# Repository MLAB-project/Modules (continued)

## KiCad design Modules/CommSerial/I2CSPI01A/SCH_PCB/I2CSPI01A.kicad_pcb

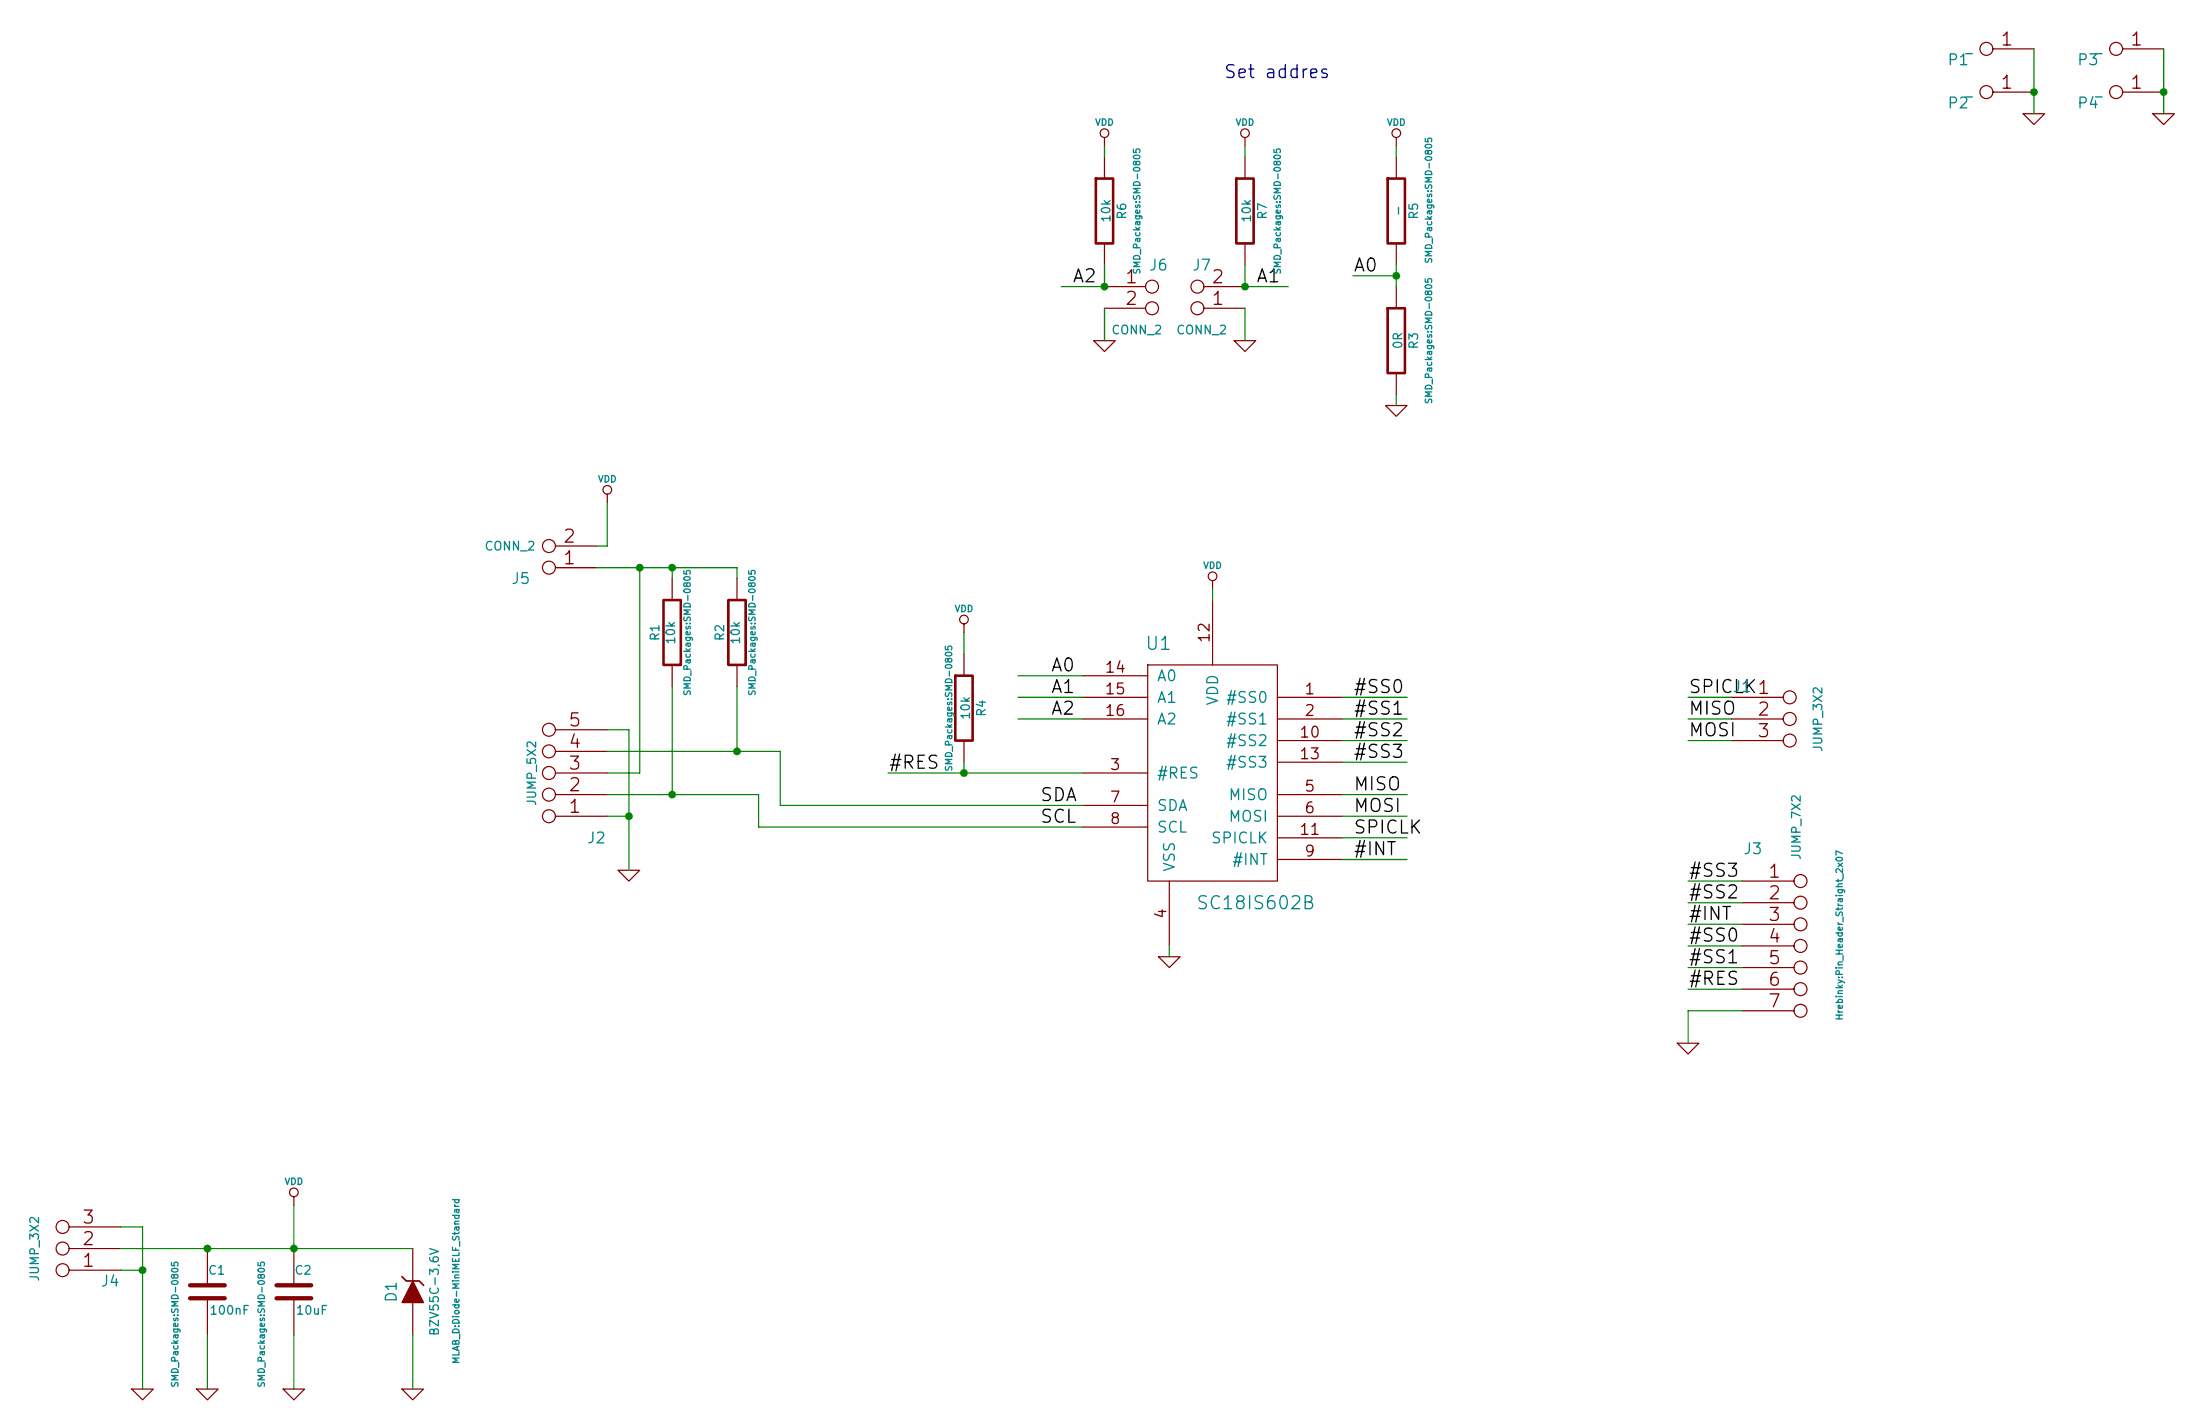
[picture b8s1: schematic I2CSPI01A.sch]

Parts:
C1: 100nF; SMD-0805
C2: 10uF; SMD-0805
D1: BZV55C-3,6V; Diode-MiniMELF_Standard
J1, J4: JUMP_3X2; Pin_Header_Straight_2x03
J2: JUMP_5X2; Pin_Header_Straight_2x05
J3: JUMP_7X2; Pin_Header_Straight_2x07
J5, J6, J7: CONN_2; Pin_Header_Straight_1x02
P1, P2, P3, P4: _; MountingHole_3mm
R1, R2, R4, R6, R7: 10k; SMD-0805
R3: 0R; SMD-0805
R5: -; SMD-0805
U1: SC18IS602B; TSSOP-16

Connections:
/#INT: J3.3, J3.12, U1.9 (#INT)
/#RES: J3.6, J3.9, R4.2, U1.3 (#RES)
/#SS0: J3.4, J3.11, U1.1 (#SS0)
/#SS1: J3.5, J3.10, U1.2 (#SS1)
/#SS2: J3.2, J3.13, U1.10 (#SS2)
/#SS3: J3.1, J3.14, U1.13 (#SS3)
/A0: R3.1, R5.2, U1.14 (A0)
/A1: J7.2 (PM), R7.2, U1.15 (A1)
/A2: J6.1, R6.2, U1.16 (A2)
/MISO: J1.2 (1), J1.5, U1.5 (MISO)
/MOSI: J1.3, J1.4, U1.6 (MOSI)
/SCL: J2.2, J2.9, R1.1, U1.8 (SCL)
/SDA: J2.4, J2.7, R2.1, U1.7 (SDA)
/SPICLK: J1.1, J1.6, U1.11 (SPICLK)
GND: C1.2, C2.2, D1.1 (A), J2.1, J2.5, J2.6, J2.10, J3.7, J3.8, J4.1, J4.3, J4.4, J4.6, J6.2 (PM), J7.1, P1.1, P2.1, P3.1, P4.1, R3.2, U1.4 (VSS)
unnamed: J2.3, J2.8, J5.1, R1.2, R2.2
VDD: C1.1, C2.1, D1.2 (K), J4.2 (1), J4.5, J5.2 (PM), R4.1, R5.1, R6.1, R7.1, U1.12 (VDD)

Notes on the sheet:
Set addres

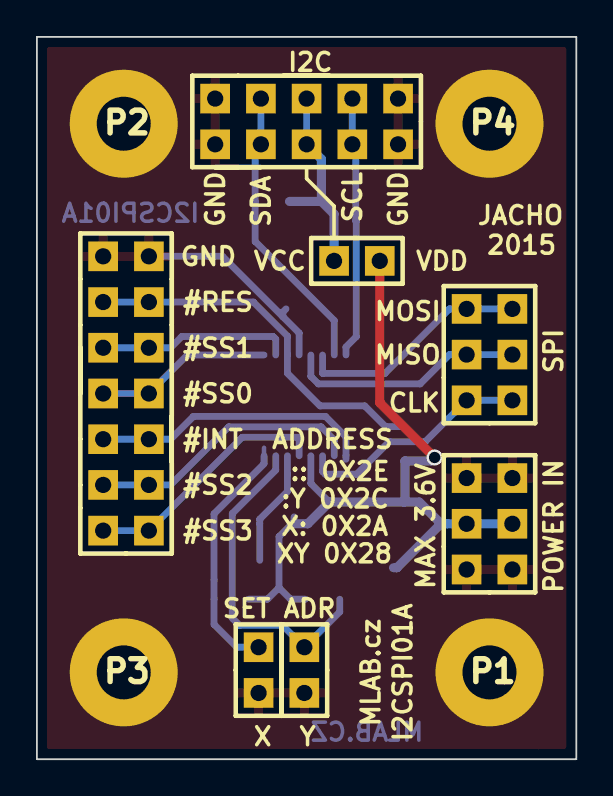
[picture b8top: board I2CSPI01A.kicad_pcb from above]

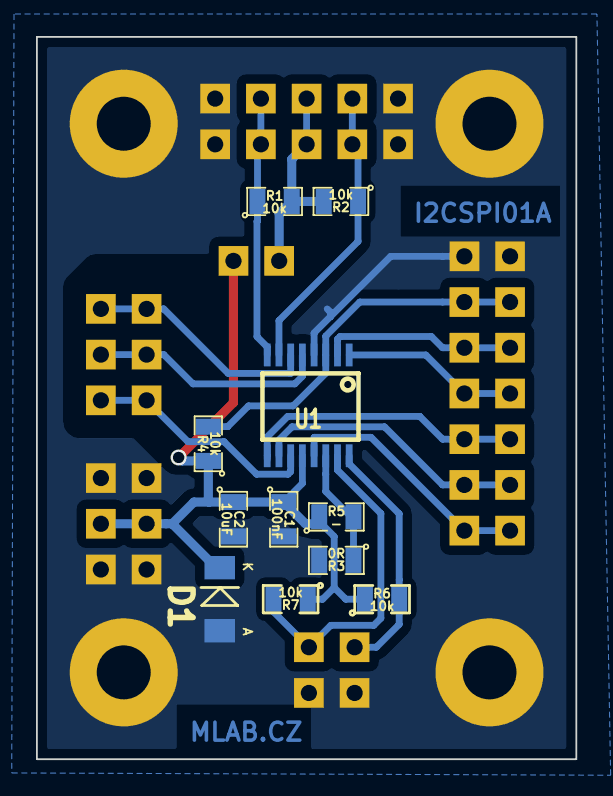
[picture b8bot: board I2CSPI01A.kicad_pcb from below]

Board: 2 copper layers, 30.0 x 40.1 mm, 22 parts (11 on the bottom side), 17 nets.
